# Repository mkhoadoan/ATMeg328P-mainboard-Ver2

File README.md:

This is the main controller board for my mechatronic project,
designed based on ATMega328P microcontrollers and other peripherals 
like ADC, motor driver, sensors, etc

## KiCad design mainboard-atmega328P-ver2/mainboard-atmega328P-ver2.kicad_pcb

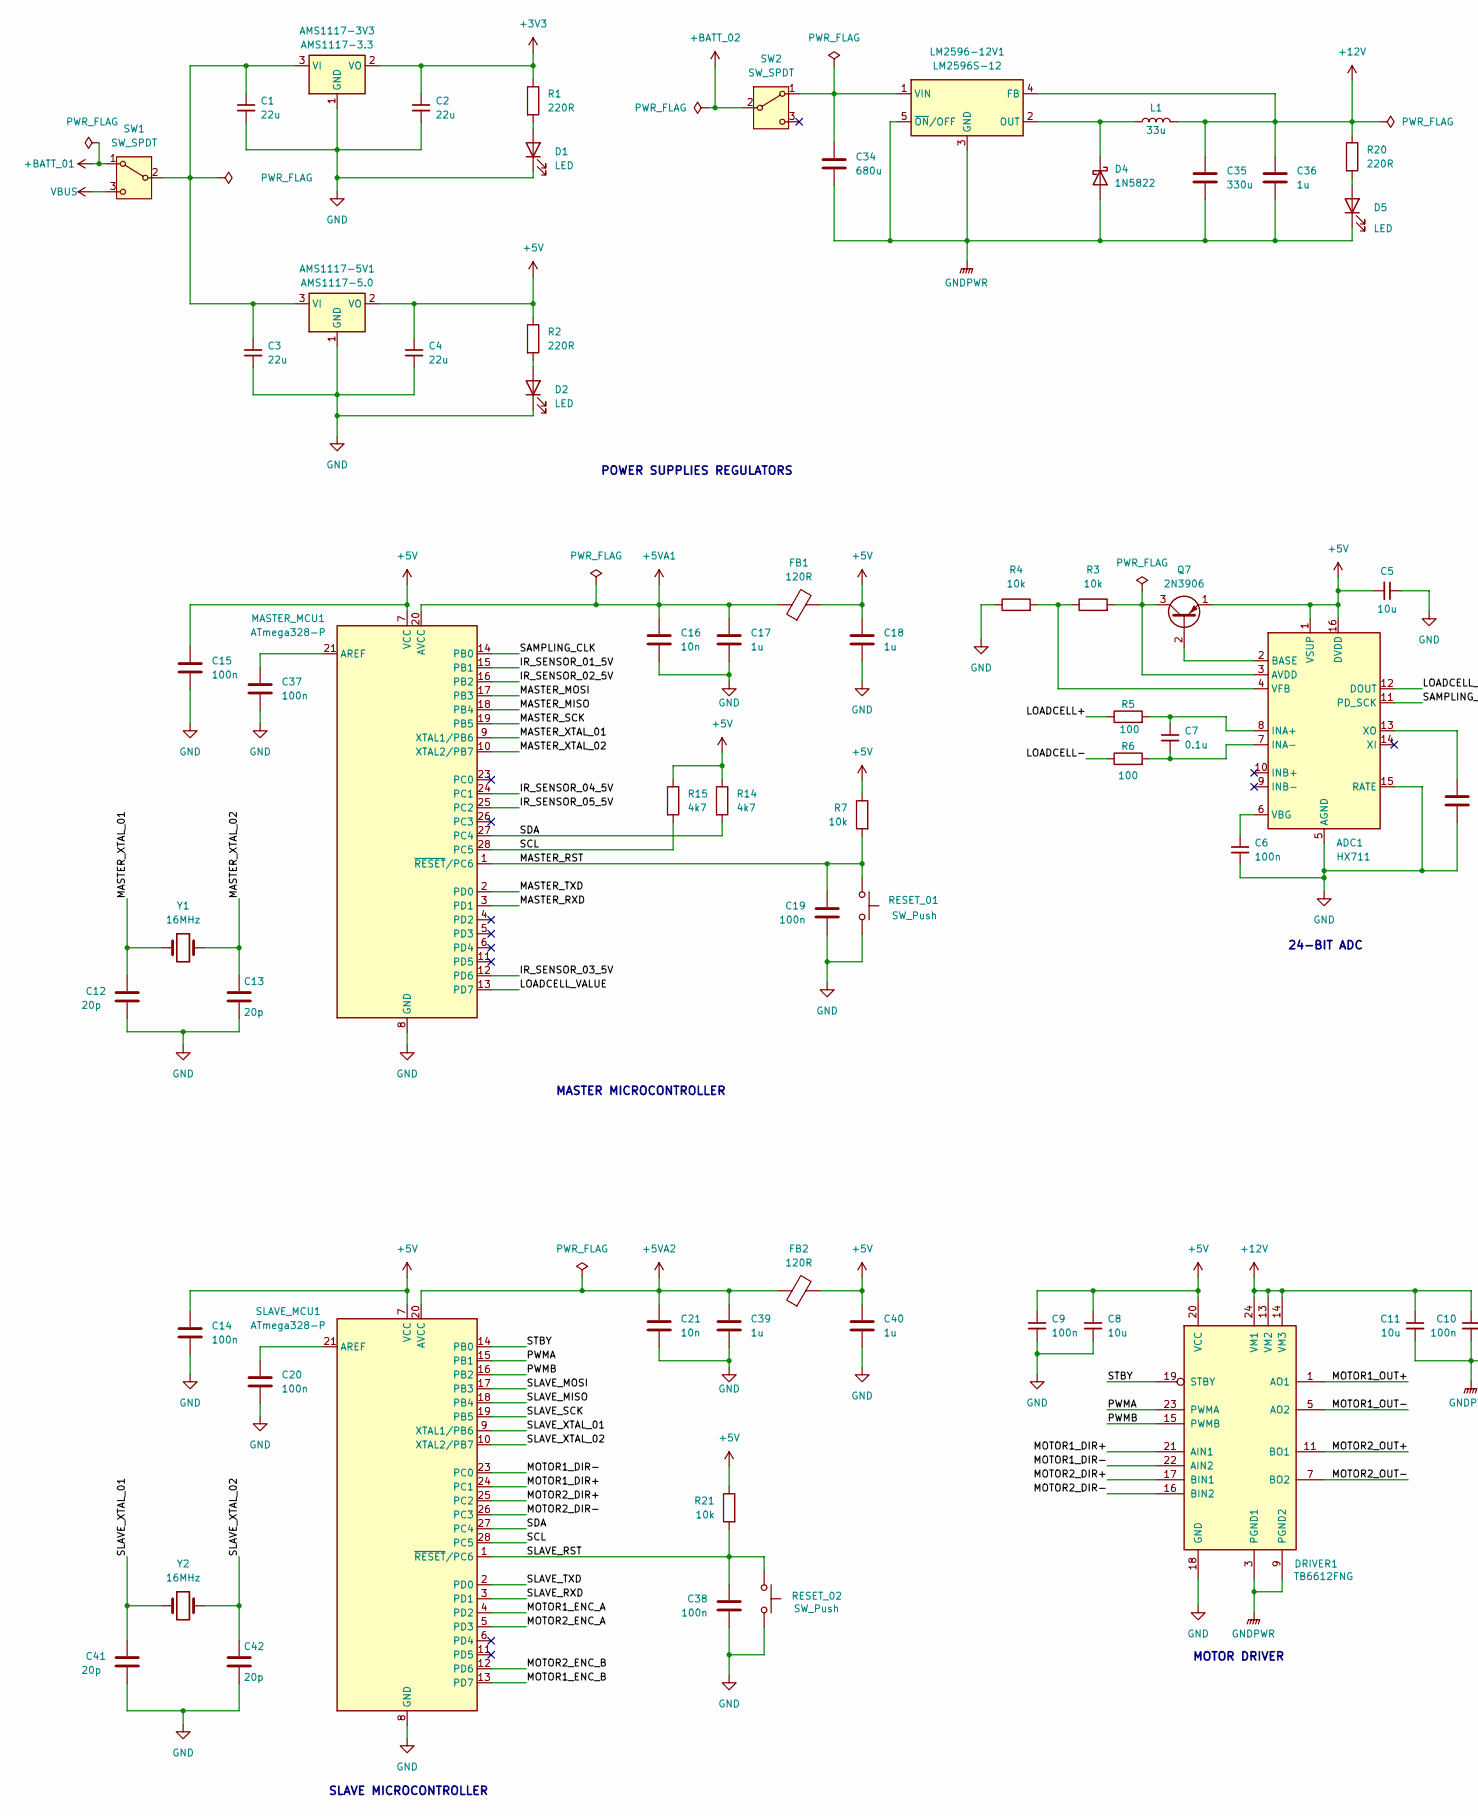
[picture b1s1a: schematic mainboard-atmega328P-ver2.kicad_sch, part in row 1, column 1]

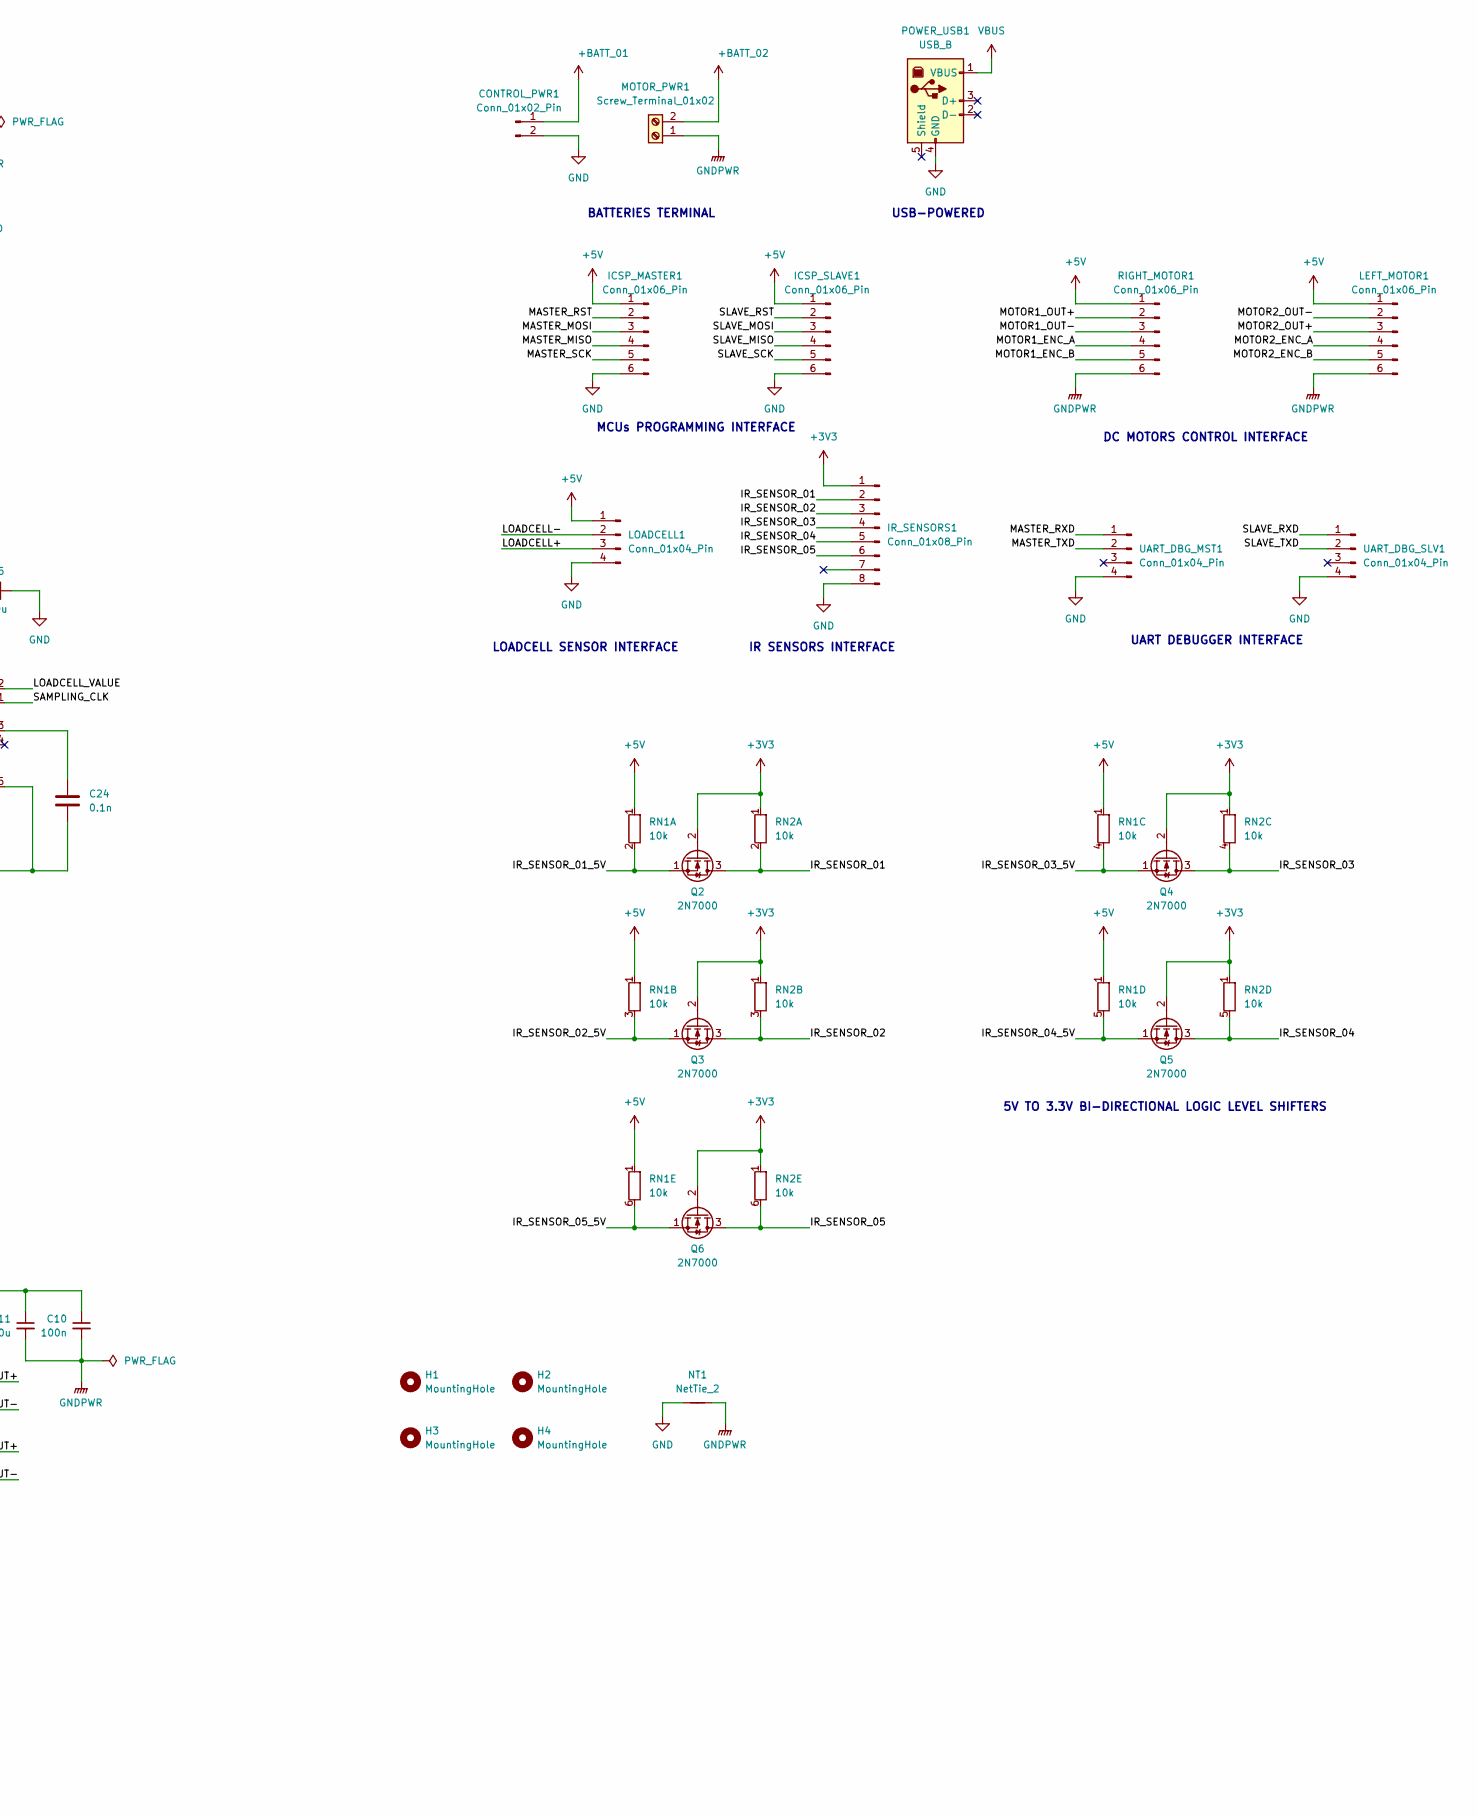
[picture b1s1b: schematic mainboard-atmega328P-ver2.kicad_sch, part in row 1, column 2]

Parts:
ADC1: HX711; SOIC-16_3.9x9.9mm_P1.27mm
AMS1117-3V3: AMS1117-3.3; SOT-223-3_TabPin2
AMS1117-5V1: AMS1117-5.0; SOT-223-3_TabPin2
C1, C2: 22u; C_0805_2012Metric
C3, C4: 22u; C_0805_2012Metric_Pad1.18x1.45mm_HandSolder
C5, C8, C11: 10u; C_0805_2012Metric_Pad1.18x1.45mm_HandSolder
C6, C9, C10, C14, C15, C20, C37: 100n; C_0805_2012Metric_Pad1.18x1.45mm_HandSolder
C7: 0.1u; C_0805_2012Metric_Pad1.18x1.45mm_HandSolder
C12, C13, C41, C42: 20p; C_0805_2012Metric_Pad1.18x1.45mm_HandSolder
C16, C21: 10n; C_0805_2012Metric_Pad1.18x1.45mm_HandSolder
C17, C18, C39, C40: 1u; C_0805_2012Metric_Pad1.18x1.45mm_HandSolder
C19, C38: 100n; C_Disc_D7.5mm_W2.5mm_P5.00mm
C24: 0.1n; C_0805_2012Metric_Pad1.18x1.45mm_HandSolder
C34: 680u; C_Radial_D5.0mm_H5.0mm_P2.00mm
C35: 330u; C_Radial_D5.0mm_H5.0mm_P2.00mm
C36: 1u; C_Radial_D5.0mm_H5.0mm_P2.00mm
CONTROL_PWR1: Conn_01x02_Pin; TE_440055-2_1x02_P2.00mm_Horizontal
D1, D2, D5: LED; LED_0805_2012Metric_Pad1.15x1.40mm_HandSolder
D4: 1N5822; D_DO-201AD_P15.24mm_Horizontal
DRIVER1: TB6612FNG; SSOP-24_5.3x8.2mm_P0.65mm
FB1, FB2: 120R; L_0805_2012Metric_Pad1.15x1.40mm_HandSolder
H1, H2, H3, H4: MountingHole; MountingHole_3.2mm_M3_Pad_TopBottom
ICSP_MASTER1: Conn_01x06_Pin; JST_EH_B6B-EH-A_1x06_P2.50mm_Vertical
ICSP_SLAVE1: Conn_01x06_Pin; JST_EH_B6B-EH-A_1x06_P2.50mm_Vertical
IR_SENSORS1: Conn_01x08_Pin; JST_EH_B8B-EH-A_1x08_P2.50mm_Vertical
L1: 33u; L_6.3x6.3_H3
LEFT_MOTOR1: Conn_01x06_Pin; JST_EH_B6B-EH-A_1x06_P2.50mm_Vertical
LM2596-12V1: LM2596S-12; TO-220-5_P3.4x3.7mm_StaggerEven_Lead3.8mm_Vertical
LOADCELL1: Conn_01x04_Pin; JST_EH_B4B-EH-A_1x04_P2.50mm_Vertical
MASTER_MCU1: ATmega328-P; DIP-28_W7.62mm
MOTOR_PWR1: Screw_Terminal_01x02; TerminalBlock_Phoenix_MKDS-1,5-2-5.08_1x02_P5.08mm_Horizont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
NT1: NetTie_2; NetTie-2_THT_Pad1.0mm
POWER_USB1: USB_B; USB_B_OST_USB-B1HSxx_Horizontal
Q2, Q3, Q4, Q5, Q6: 2N7000; TO-92_Inline
Q7: 2N3906; TO-92_Inline
R1: 220R; R_0805_2012Metric
R2, R20: 220R; R_0805_2012Metric_Pad1.20x1.40mm_HandSolder
R3, R4, R7, R21: 10k; R_Axial_DIN0204_L3.6mm_D1.6mm_P5.08mm_Horizontal
R5, R6: 100; R_Axial_DIN0204_L3.6mm_D1.6mm_P5.08mm_Horizontal
R14, R15: 4k7; R_Axial_DIN0207_L6.3mm_D2.5mm_P10.16mm_Horizontal
RESET_01, RESET_02: SW_Push; SW_TH_Tactile_Omron_B3F-102x
RIGHT_MOTOR1: Conn_01x06_Pin; JST_EH_B6B-EH-A_1x06_P2.50mm_Vertical
RN1, RN2: 10k; R_Array_SIP6
SLAVE_MCU1: ATmega328-P; DIP-28_W7.62mm
SW1, SW2: SW_SPDT; SW_Slide_SPDT_Straight_CK_OS102011MS2Q
UART_DBG_MST1: Conn_01x04_Pin; PinHeader_1x04_P2.54mm_Horizontal
UART_DBG_SLV1: Conn_01x04_Pin; PinHeader_1x04_P2.54mm_Horizontal
Y1, Y2: 16MHz; Crystal_HC49-4H_Vertical

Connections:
+3V3: AMS1117-3V3.2 (VO), C2.1, IR_SENSORS1.1, Q2.2 (G), Q3.2 (G), Q4.2 (G), Q5.2 (G), Q6.2 (G), R1.1, RN2.1 (R1)
+5V: ADC1.1 (VSUP), ADC1.16 (DVDD), AMS1117-5V1.2 (VO), C4.1, C5.2, C8.1, C9.1, C14.1, C15.1, C18.1, C40.1, DRIVER1.20 (VCC), FB1.2, FB2.2, ICSP_MASTER1.1, ICSP_SLAVE1.1, LEFT_MOTOR1.1, LOADCELL1.1, MASTER_MCU1.7 (VCC), Q7.1 (E), R2.1, R7.1, R14.1, R15.1, R21.1, RIGHT_MOTOR1.1, RN1.1 (R1), SLAVE_MCU1.7 (VCC)
+5VA1: C16.1, C17.1, FB1.1, MASTER_MCU1.20 (AVCC)
+5VA2: C21.1, C39.1, FB2.1, SLAVE_MCU1.20 (AVCC)
+12V: C10.1, C11.1, C35.1, C36.1, DRIVER1.13 (VM2), DRIVER1.14 (VM3), DRIVER1.24 (VM1), L1.2, LM2596-12V1.4 (FB), R20.1
+BATT_01: CONTROL_PWR1.1, SW1.1 (A)
+BATT_02: MOTOR_PWR1.2, SW2.2 (B)
/IR_SENSOR_01: IR_SENSORS1.2, Q2.3 (D), RN2.2 (R1.2)
/IR_SENSOR_01_5V: MASTER_MCU1.15 (PB1), Q2.1 (S), RN1.2 (R1.2)
/IR_SENSOR_02: IR_SENSORS1.3, Q3.3 (D), RN2.3 (R2.2)
/IR_SENSOR_02_5V: MASTER_MCU1.16 (PB2), Q3.1 (S), RN1.3 (R2.2)
/IR_SENSOR_03: IR_SENSORS1.4, Q4.3 (D), RN2.4 (R3.2)
/IR_SENSOR_03_5V: MASTER_MCU1.12 (PD6), Q4.1 (S), RN1.4 (R3.2)
/IR_SENSOR_04: IR_SENSORS1.5, Q5.3 (D), RN2.5 (R4.2)
/IR_SENSOR_04_5V: MASTER_MCU1.24 (PC1), Q5.1 (S), RN1.5 (R4.2)
/IR_SENSOR_05: IR_SENSORS1.6, Q6.3 (D), RN2.6 (R5.2)
/IR_SENSOR_05_5V: MASTER_MCU1.25 (PC2), Q6.1 (S), RN1.6 (R5.2)
/LOADCELL+: LOADCELL1.3, R5.1
/LOADCELL-: LOADCELL1.2, R6.1
/LOADCELL_VALUE: ADC1.12 (DOUT), MASTER_MCU1.13 (PD7)
/MASTER_MISO: ICSP_MASTER1.4, MASTER_MCU1.18 (PB4)
/MASTER_MOSI: ICSP_MASTER1.3, MASTER_MCU1.17 (PB3)
/MASTER_RST: C19.1, ICSP_MASTER1.2, MASTER_MCU1.1 (~RESET/PC6), R7.2, RESET_01.2
/MASTER_RXD: MASTER_MCU1.3 (PD1), UART_DBG_MST1.1
/MASTER_SCK: ICSP_MASTER1.5, MASTER_MCU1.19 (PB5)
/MASTER_TXD: MASTER_MCU1.2 (PD0), UART_DBG_MST1.2
/MASTER_XTAL_01: C12.1, MASTER_MCU1.9 (XTAL1/PB6), Y1.1
/MASTER_XTAL_02: C13.1, MASTER_MCU1.10 (XTAL2/PB7), Y1.2
/MOTOR1_DIR+: DRIVER1.21 (AIN1), SLAVE_MCU1.24 (PC1)
/MOTOR1_DIR-: DRIVER1.22 (AIN2), SLAVE_MCU1.23 (PC0)
/MOTOR1_ENC_A: RIGHT_MOTOR1.4, SLAVE_MCU1.4 (PD2)
/MOTOR1_ENC_B: RIGHT_MOTOR1.5, SLAVE_MCU1.13 (PD7)
/MOTOR1_OUT+: DRIVER1.1 (AO1), DRIVER1.2 (AO1), RIGHT_MOTOR1.2
/MOTOR1_OUT-: DRIVER1.5 (AO2), DRIVER1.6 (AO2), RIGHT_MOTOR1.3
/MOTOR2_DIR+: DRIVER1.17 (BIN1), SLAVE_MCU1.25 (PC2)
/MOTOR2_DIR-: DRIVER1.16 (BIN2), SLAVE_MCU1.26 (PC3)
/MOTOR2_ENC_A: LEFT_MOTOR1.4, SLAVE_MCU1.5 (PD3)
/MOTOR2_ENC_B: LEFT_MOTOR1.5, SLAVE_MCU1.12 (PD6)
/MOTOR2_OUT+: DRIVER1.11 (BO1), DRIVER1.12 (BO1), LEFT_MOTOR1.3
/MOTOR2_OUT-: DRIVER1.7 (BO2), DRIVER1.8 (BO2), LEFT_MOTOR1.2
/PWMA: DRIVER1.23 (PWMA), SLAVE_MCU1.15 (PB1)
/PWMB: DRIVER1.15 (PWMB), SLAVE_MCU1.16 (PB2)
/SAMPLING_CLK: ADC1.11 (PD_SCK), MASTER_MCU1.14 (PB0)
/SCL: MASTER_MCU1.28 (PC5), R15.2, SLAVE_MCU1.28 (PC5)
/SDA: MASTER_MCU1.27 (PC4), R14.2, SLAVE_MCU1.27 (PC4)
/SLAVE_MISO: ICSP_SLAVE1.4, SLAVE_MCU1.18 (PB4)
/SLAVE_MOSI: ICSP_SLAVE1.3, SLAVE_MCU1.17 (PB3)
/SLAVE_RST: C38.1, ICSP_SLAVE1.2, R21.2, RESET_02.2, SLAVE_MCU1.1 (~RESET/PC6)
/SLAVE_RXD: SLAVE_MCU1.3 (PD1), UART_DBG_SLV1.1
/SLAVE_SCK: ICSP_SLAVE1.5, SLAVE_MCU1.19 (PB5)
/SLAVE_TXD: SLAVE_MCU1.2 (PD0), UART_DBG_SLV1.2
/SLAVE_XTAL_01: C41.1, SLAVE_MCU1.9 (XTAL1/PB6), Y2.1
/SLAVE_XTAL_02: C42.1, SLAVE_MCU1.10 (XTAL2/PB7), Y2.2
/STBY: DRIVER1.19 (STBY), SLAVE_MCU1.14 (PB0)
GND: ADC1.5 (AGND), ADC1.15 (RATE), AMS1117-3V3.1 (GND), AMS1117-5V1.1 (GND), C1.2, C2.2, C3.2, C4.2, C5.1, C6.2, C8.2, C9.2, C12.2, C13.2, C14.2, C15.2, C16.2, C17.2, C18.2, C19.2, C20.2, C21.2, C24.2, C37.2, C38.2, C39.2, C40.2, C41.2, C42.2, CONTROL_PWR1.2, D1.1 (K), D2.1 (K), DRIVER1.18 (GND), ICSP_MASTER1.6, ICSP_SLAVE1.6, IR_SENSORS1.8, LOADCELL1.4, MASTER_MCU1.8 (GND), MASTER_MCU1.22 (GND), NT1.1, POWER_USB1.4 (GND), R4.1, RESET_01.1, RESET_02.1, SLAVE_MCU1.8 (GND), SLAVE_MCU1.22 (GND), UART_DBG_MST1.4, UART_DBG_SLV1.4
GNDPWR: C10.2, C11.2, C34.2, C35.2, C36.2, D4.2 (A), D5.1 (K), DRIVER1.3 (PGND1), DRIVER1.4 (PGND1), DRIVER1.9 (PGND2), DRIVER1.10 (PGND2), LEFT_MOTOR1.6, LM2596-12V1.3 (GND), LM2596-12V1.5 (~ON/OFF), MOTOR_PWR1.1, NT1.2, RIGHT_MOTOR1.6
unnamed: ADC1.3 (AVDD), Q7.3 (C), R3.2
unnamed: ADC1.2 (BASE), Q7.2 (B)
unnamed: ADC1.8 (INA+), C7.1, R5.2
unnamed: ADC1.7 (INA-), C7.2, R6.2
unnamed: ADC1.6 (VBG), C6.1
unnamed: ADC1.4 (VFB), R3.1, R4.2
unnamed: ADC1.13 (XO), C24.1
unnamed: AMS1117-3V3.3 (VI), AMS1117-5V1.3 (VI), C1.1, C3.1, SW1.2 (B)
unnamed: D1.2 (A), R1.2
unnamed: D2.2 (A), R2.2
unnamed: D4.1 (K), L1.1, LM2596-12V1.2 (OUT)
unnamed: D5.2 (A), R20.2
unnamed: C34.1, LM2596-12V1.1 (VIN), SW2.1 (A)
unnamed: C37.1, MASTER_MCU1.21 (AREF)
unnamed: C20.1, SLAVE_MCU1.21 (AREF)
VBUS: POWER_USB1.1 (VBUS), SW1.3 (C)

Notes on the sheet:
SLAVE MICROCONTROLLER
5V TO 3.3V BI-DIRECTIONAL LOGIC LEVEL SHIFTERS
MOTOR DRIVER
DC MOTORS CONTROL INTERFACE
USB-POWERED
POWER SUPPLIES REGULATORS
24-BIT ADC
MCUs PROGRAMMING INTERFACE
MASTER MICROCONTROLLER
UART DEBUGGER INTERFACE
BATTERIES TERMINAL
IR SENSORS INTERFACE
LOADCELL SENSOR INTERFACE

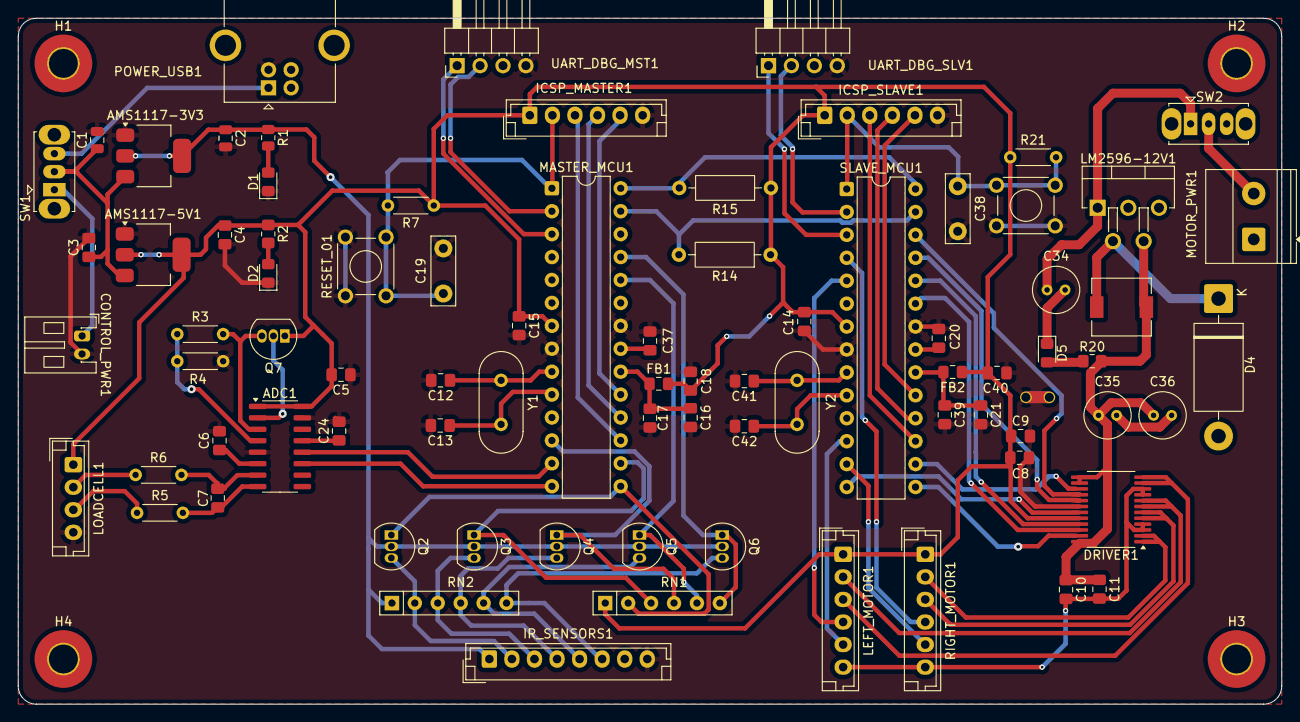
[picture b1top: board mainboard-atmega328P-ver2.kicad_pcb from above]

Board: 2 copper layers, 140.0 x 76.0 mm, 86 parts (0 on the bottom side), 72 nets.

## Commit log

2025-11-05 Add files via upload
    Main controller board for mechatronics projects, including schematic, pcb and gerber
2025-11-05 Add project description to README.md
